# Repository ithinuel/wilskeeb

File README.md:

# Wil's Keyboard

This project implements a split keyboard based on the [Redox](https://github.com/mattdibi/redox-keyboard)
PCB but powered by a [SparkFun Pro Micro - RP2040](https://www.sparkfun.com/products/18288).

It features:

- Automatic main-secondary detection (either side can be connected to usb)
- Automatic chirality detection allowing the same binary to run on both sides.
- A virtual serial port to a simple CLI to help with debugging & update.
- 128x64 (SH1107 based) Oled display support

Extra optional features are also available:

- RGB Led strip

The communication between main & secondary is done through an I²C interface.

## Firmware deployment

On a fresh RP2040 enter into bootload by maintaining the boot button pressed while pressing reset.
Then run `cargo run --release` to compile and flash the firmware.

Refer to defmt documentation for available logging parameters.

I used the following command to update the firmware after the case is assembled and the buttons are
no-longer accessible.

```sh
DEFMT_BBQ_BUFFER_SIZE=4096 DEFMT_LOG=trace cargo build --release && echo -n u >> [your-uart] && sleep 5 && elf2uf2-rs -d target/thumbv6m-none-eabi/release/wilskeeb
```

## Layout

%2F%3B%3B&radii=20px&pcb:true&plate:false%3B&@_x:3.25&t=%23000000%0A%0A%23ff0000%3B&=%23%0A3%0AF3&_x:9&t=%23000000%3B&=*%0A8%3B&@_y:-0.875&x:2.25&t=%23000000%0A%0A%23ff0000%3B&=%2F@%0A2%0AF2&_x:1%3B&=$%0A4%0AF4&_x:7&t=%23000000%3B&=%2F&%0A7&_x:1%3B&=(%0A9%3B&@_y:-0.905&x:5.25&t=%23000000%0A%0A%23ff0000%3B&=%25%0A5%0AF5&_x:5&t=%23000000%3B&=%5E%0A6%3B&@_y:-0.845&a:5&w:1.25%3B&=~%0A%60&_t=%23000000%0A%0A%23ff0000&a:4%3B&=!%0A1%0AF1&_x:13&t=%23000000%3B&=)%0A0&_w:1.25%3B&=%7B%0A%5B%3B&@_y:-0.655&x:6.25&t=%23000000%0A%0A%23ff0000%3B&=%0A%0AF6&_x:3&t=%23000000&a:7%3B&=%3B&@_y:-0.72&x:3.25&t=%23000000%0A%0A%23ff0000&a:4%3B&=E%0A%0AF9&_x:9%3B&=I%0A%0A%3Ci%20class%2F='fa%20fa-arrow-up'%3E%3C%2F%2Fi%3E%3B&@_y:-0.875&x:2.25%3B&=W%0A%0AF8&_x:1%3B&=R%0A%0AF10&_x:7&fa@:0&:0&:5%3B%3B&=U%0A%0A%3Ci%20class%2F='kb%20kb-Arrows-Top-2'%3E%3C%2F%2Fi%3E&_x:1%3B&=O%0A%0A%3Ci%20class%2F='kb%20kb-Arrows-Bottom-2'%3E%3C%2F%2Fi%3E%3B&@_y:-0.905&x:5.25&f:3%3B&=T%0A%0AF11&_x:5&f:3%3B&=Y%0A%0A%3Ci%20class%2F='kb%20kb-Unicode-Page-Up-3'%3E%3C%2F%2Fi%3E%3B&@_y:-0.845&t=%23000000&a:7&fa@:7%3B&w:1.25%3B&=%3Ci%20class%2F='kb%20kb-Line-Start-End'%3E%3C%2F%2Fi%3E&_t=%23000000%0A%0A%23ff0000&a:4&f:3%3B&=Q%0A%0AF7%3B&@_y:-1&x:15.25&t=%23000000&f:3%3B&=P&_f:3&w:1.25%3B&=%7D%0A%5D%3B&@_y:-0.655&x:6.25&t=%23000000%0A%0A%23ff0000&h:1.5%3B&=%0A%0AF12&_x:3&t=%23000000&a:7&h:1.5%3B&=%3B&@_y:-0.72&x:3.25&a:4&f:3%3B&=D%3B&@_y:-1&x:13.25&t=%23000000%0A%0A%23ff0000&f:3%3B&=K%0A%0A%3Ci%20class%2F='fa%20fa-arrow-down'%3E%3C%2F%2Fi%3E%3B&@_y:-0.875&x:2.25&t=%23000000&f:3%3B&=S&_x:1&f:3&n:true%3B&=F&_x:7&t=%23000000%0A%0A%23ff0000%0A%23008000&f:3&n:true%3B&=J%0A%0A%3Ci%20class%2F='fa%20fa-arrow-left'%3E%3C%2F%2Fi%3E%0A%3Ci%20class%2F='kb%20kb-Multimedia-Rewind-Start'%3E%3C%2F%2Fi%3E&_x:1&f:3%3B&=L%0A%0A%3Ci%20class%2F='fa%20fa-arrow-right'%3E%3C%2F%2Fi%3E%0A%3Ci%20class%2F='kb%20kb-Multimedia-FastForward-End'%3E%3C%2F%2Fi%3E%3B&@_y:-0.9049999999999998&x:5.25&t=%23000000&f:3%3B&=G&_x:5&t=%23000000%0A%0A%23ff0000&fa@:0&:0&:5%3B%3B&=H%0A%0A%3Ci%20class%2F='kb%20kb-Unicode-Page-Down-3'%3E%3C%2F%2Fi%3E%3B&@_y:-0.8450000000000002&t=%23000000&a:7&w:1.25%3B&=Shift&_a:4%3B&=A&_x:13%3B&=%2F:%0A%2F%3B&_w:1.25%3B&=%2F@%0A'%3B&@_y:-0.375&x:3.25%3B&=C&_x:9%3B&=%3C%0A,%3B&@_y:-0.875&x:2.25%3B&=X&_x:1%3B&=V&_x:7%3B&=M&_x:1%3B&=%3E%0A.%3B&@_y:-0.9049999999999998&x:5.25%3B&=B&_x:5%3B&=N%3B&@_y:-0.8450000000000006&a:7&w:1.25%3B&=Ctrl&_a:4%3B&=Z&_x:13%3B&=%3F%0A%2F%2F&_w:1.25%3B&=~%0A%23%3B&@_y:-0.375&x:3.25&a:7%3B&=LAlt&_x:9&fa@:6%3B%3B&=%3Ci%20class%2F='fa%20fa-stack-overflow'%3E%3C%2F%2Fi%3E%3B&@_y:-0.875&x:2.25%3B&=&_x:11&a:4&f:3%3B&=%2F_%0A-%3B&@_y:-0.75&x:0.25&a:6&f:3%3B&=Pause&_f:3%3B&=PrtSc&_x:13&a:4&f:3%3B&=+%0A%2F=&_a:7&fa@:7%3B%3B&=%3Ci%20class%2F='fa%20fa-list-alt'%3E%3C%2F%2Fi%3E%3B&@_r:25&rx:5.135&ry:4.845&y:-0.5&x:-0.5&f:3%3B&=Esc%3B&@_r:30&rx:7.068&ry:4.875&y:-1&x:-1%3B&=&_f:3%3B&=Ins%3B&@_x:-1&f:3&h:1.5%3B&=%3Ci%20class%2F='kb%20kb-Return-2'%3E%3C%2F%2Fi%3E&_f:3&h:1.5%3B&=Space%3B&@_r:-30&rx:10.432&y:-1&x:-1&f:3%3B&=Del&_c=%232aa50a&f:3%3B&=Fn2%3B&@_x:-1&c=%23cccccc&f:3&h:1.5%3B&=%3Ci%20class%2F='kb%20kb-Arrows-Left'%3E%3C%2F%2Fi%3E&_c=%23ff0000&f:3&h:1.5%3B&=Fn1%3B&@_r:-25&rx:12.365&ry:4.845&y:-0.5&x:-0.5&c=%23cccccc&f:3%3B&=AltGr)

## Licenses

The hardware design files present in this repository under the `pcb` and `case` directories are
distributed under the [CERN OHL S v2 License](./cern_ohl_s_v2.txt).

```text
Copyright Wilfried Chauveau 2022.

This source describes Open Hardware and is licensed under the CERN-OHL-S v2.
You may redistribute and modify this source and make products using it under
the terms of the CERN-OHL-S v2 (https://ohwr.org/cern_ohl_s_v2.txt).

This source is distributed WITHOUT ANY EXPRESS OR IMPLIED WARRANTY, INCLUDING
OF MERCHANTABILITY, SATISFACTORY QUALITY AND FITNESS FOR A PARTICULAR PURPOSE.
Please see the CERN-OHL-S v2 for applicable conditions.

Source location: https://github.com/ithinuel/wilskeeb.git

As per CERN-OHL-S v2 section 4, should You produce hardware based on this source,
You must where practicable maintain the Source Location visible on the external
case of the Gizmo or other products you make using this source.
```

The sources available under the `firmware` directory are distributed under the
[Apache 2](./Apache-2.0.txt) license.

```text
Copyright 2022 Wilfried Chauveau

Licensed under the Apache License, Version 2.0 (the "License");
you may not use this file except in compliance with the License.
You may obtain a copy of the License at

    http://www.apache.org/licenses/LICENSE-2.0

Unless required by applicable law or agreed to in writing, software
distributed under the License is distributed on an "AS IS" BASIS,
WITHOUT WARRANTIES OR CONDITIONS OF ANY KIND, either express or implied.
See the License for the specific language governing permissions and
limitations under the License.
```

## Extra resources

- The 3D model for the Audio jack is available at : [Kicad-packages3D − MR#495](https://gitlab.com/kicad/libraries/kicad-packages3D/-/merge_requests/495)
- The PCB design for the OLED display can be found at : [Github − Adafruit OLED FeatherWing PCB](https://github.com/adafruit/Adafruit-OLED-FeatherWing-PCB.git)
- The PCB design for the Pro Micro RP2040 can be found at : [Github − SparkFun Pro Micro RP2040](https://github.com/sparkfun/SparkFun_Pro_Micro-RP2040.git)

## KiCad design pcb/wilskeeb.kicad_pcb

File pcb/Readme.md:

# PCD Design

## Option considered

- on board per key rgb LED using WS2812-2020  
  Those RGB LED draw up to 20mA and there would be 35 of them. This plus the rest of the system would
  exceed the capacity of the USB port.

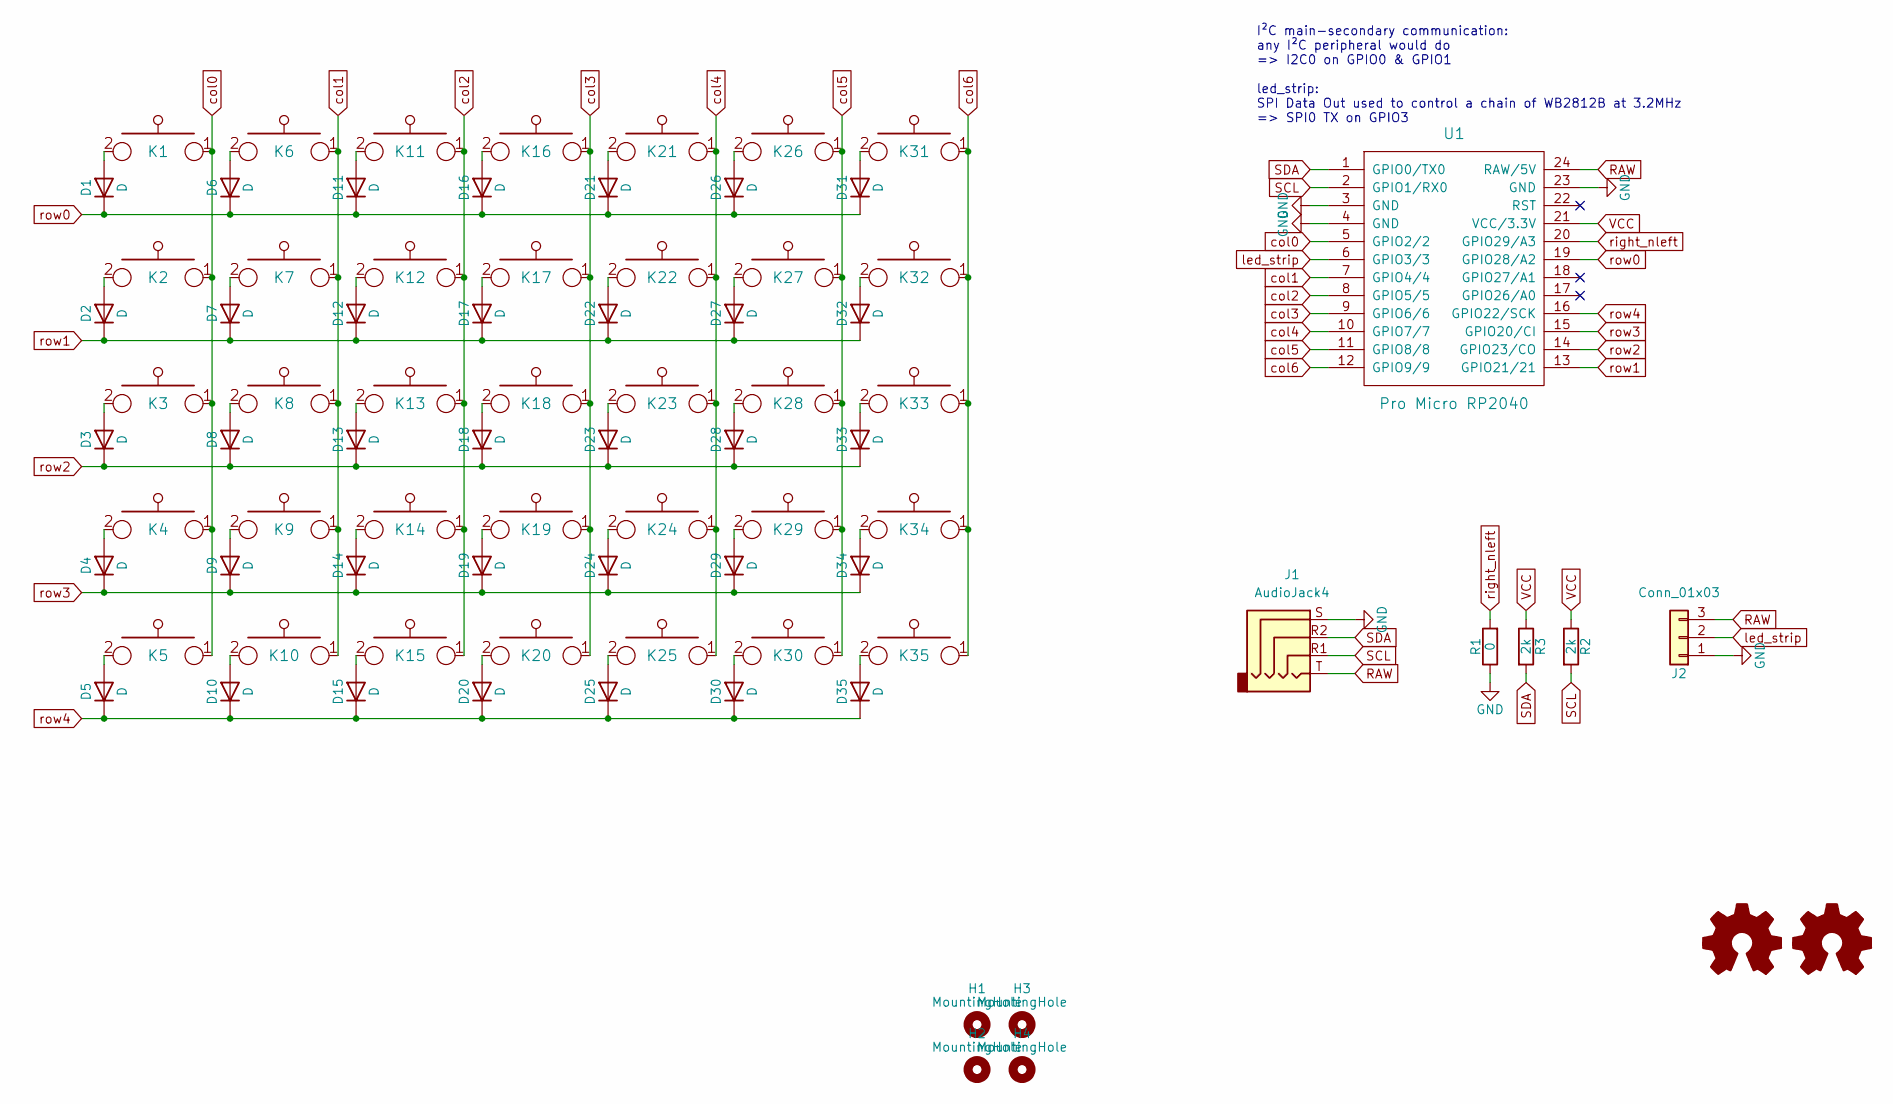
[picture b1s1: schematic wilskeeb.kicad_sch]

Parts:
D1, D2, D3, D4, D5, D6, D7, D8, D9, D10, D11, D12, D13, D14, D15, D16, D17, D18, D19, D20, D21, D22, D23, D24, D25, D26, D27, D28, D29, D30, D31, D32, D33, D34, D35: D; Diode-Hybrid-Reversible
H1, H2, H3, H4: MountingHole; MountingHole_3.2mm_M3_ISO14580
J1: AudioJack4; Jack_3.5mm_TRRS_PJ320D_Reversible
J2: Conn_01x03; PinHeader_1x03_P2.54mm_Horizontal
K1, K2, K3, K4, K5, K6, K7, K8, K9, K10, K11, K12, K13, K14, K15, K16, K17, K18, K19, K20, K21, K22, K23, K24, K25, K26, K27, K28, K29, K30, K31, K32, K33, K34, K35: KEYSW; PG1350-1u-Reversible
R1: 0; Resistor-Hybrid-Reversible
R2, R3: 2k; Resistor-Hybrid-Reversible
U1: Pro Micro RP2040; ProMicro-Reversible

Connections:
GND: J1.S, J2.1, R1.1, U1.3 (GND), U1.4 (GND), U1.23 (GND)
unnamed: D1.2 (A), K1.2
unnamed: D2.2 (A), K2.2
unnamed: D3.2 (A), K3.2
unnamed: D4.2 (A), K4.2
unnamed: D5.2 (A), K5.2
unnamed: D6.2 (A), K6.2
unnamed: D7.2 (A), K7.2
unnamed: D8.2 (A), K8.2
unnamed: D9.2 (A), K9.2
unnamed: D10.2 (A), K10.2
unnamed: D11.2 (A), K11.2
unnamed: D12.2 (A), K12.2
unnamed: D13.2 (A), K13.2
unnamed: D14.2 (A), K14.2
unnamed: D15.2 (A), K15.2
unnamed: D16.2 (A), K16.2
unnamed: D17.2 (A), K17.2
unnamed: D18.2 (A), K18.2
unnamed: D19.2 (A), K19.2
unnamed: D20.2 (A), K20.2
unnamed: D21.2 (A), K21.2
unnamed: D22.2 (A), K22.2
unnamed: D23.2 (A), K23.2
unnamed: D24.2 (A), K24.2
unnamed: D25.2 (A), K25.2
unnamed: D26.2 (A), K26.2
unnamed: D27.2 (A), K27.2
unnamed: D28.2 (A), K28.2
unnamed: D29.2 (A), K29.2
unnamed: D30.2 (A), K30.2
unnamed: D31.2 (A), K31.2
unnamed: D32.2 (A), K32.2
unnamed: D33.2 (A), K33.2
unnamed: D34.2 (A), K34.2
unnamed: D35.2 (A), K35.2
RAW: J1.T, J2.3, U1.24 (RAW/5V)
SCL: J1.R1, R2.2, U1.2 (GPIO1/RX0)
SDA: J1.R2, R3.2, U1.1 (GPIO0/TX0)
VCC: R2.1, R3.1, U1.21 (VCC/3.3V)
col0: K1.1, K2.1, K3.1, K4.1, K5.1, U1.5 (GPIO2/2)
col1: K6.1, K7.1, K8.1, K9.1, K10.1, U1.7 (GPIO4/4)
col2: K11.1, K12.1, K13.1, K14.1, K15.1, U1.8 (GPIO5/5)
col3: K16.1, K17.1, K18.1, K19.1, K20.1, U1.9 (GPIO6/6)
col4: K21.1, K22.1, K23.1, K24.1, K25.1, U1.10 (GPIO7/7)
col5: K26.1, K27.1, K28.1, K29.1, K30.1, U1.11 (GPIO8/8)
col6: K31.1, K32.1, K33.1, K34.1, K35.1, U1.12 (GPIO9/9)
led_strip: J2.2, U1.6 (GPIO3/3)
right_nleft: R1.2, U1.20 (GPIO29/A3)
row0: D1.1 (K), D6.1 (K), D11.1 (K), D16.1 (K), D21.1 (K), D26.1 (K), D31.1 (K), U1.19 (GPIO28/A2)
row1: D2.1 (K), D7.1 (K), D12.1 (K), D17.1 (K), D22.1 (K), D27.1 (K), D32.1 (K), U1.13 (GPIO21/21)
row2: D3.1 (K), D8.1 (K), D13.1 (K), D18.1 (K), D23.1 (K), D28.1 (K), D33.1 (K), U1.14 (GPIO23/CO)
row3: D4.1 (K), D9.1 (K), D14.1 (K), D19.1 (K), D24.1 (K), D29.1 (K), D34.1 (K), U1.15 (GPIO20/CI)
row4: D5.1 (K), D10.1 (K), D15.1 (K), D20.1 (K), D25.1 (K), D30.1 (K), D35.1 (K), U1.16 (GPIO22/SCK)

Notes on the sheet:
I²C main-secondary communication: any I²C peripheral would do => I2C0 on GPIO0 & GPIO1 led_strip: SPI Data Out used to control a chain of WB2812B at 3.2MHz => SPI0 TX on GPIO3

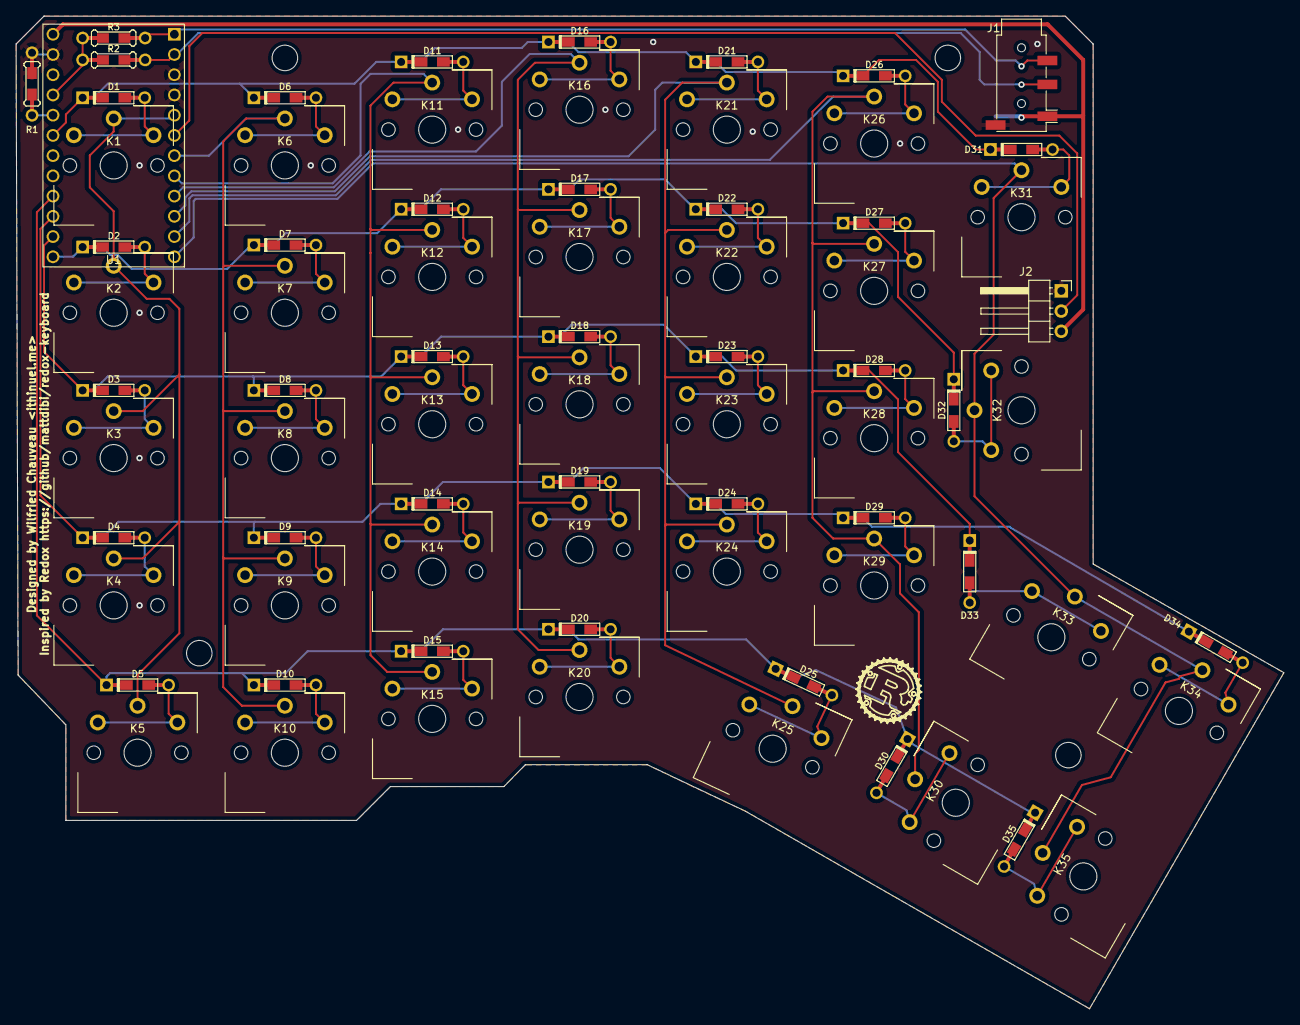
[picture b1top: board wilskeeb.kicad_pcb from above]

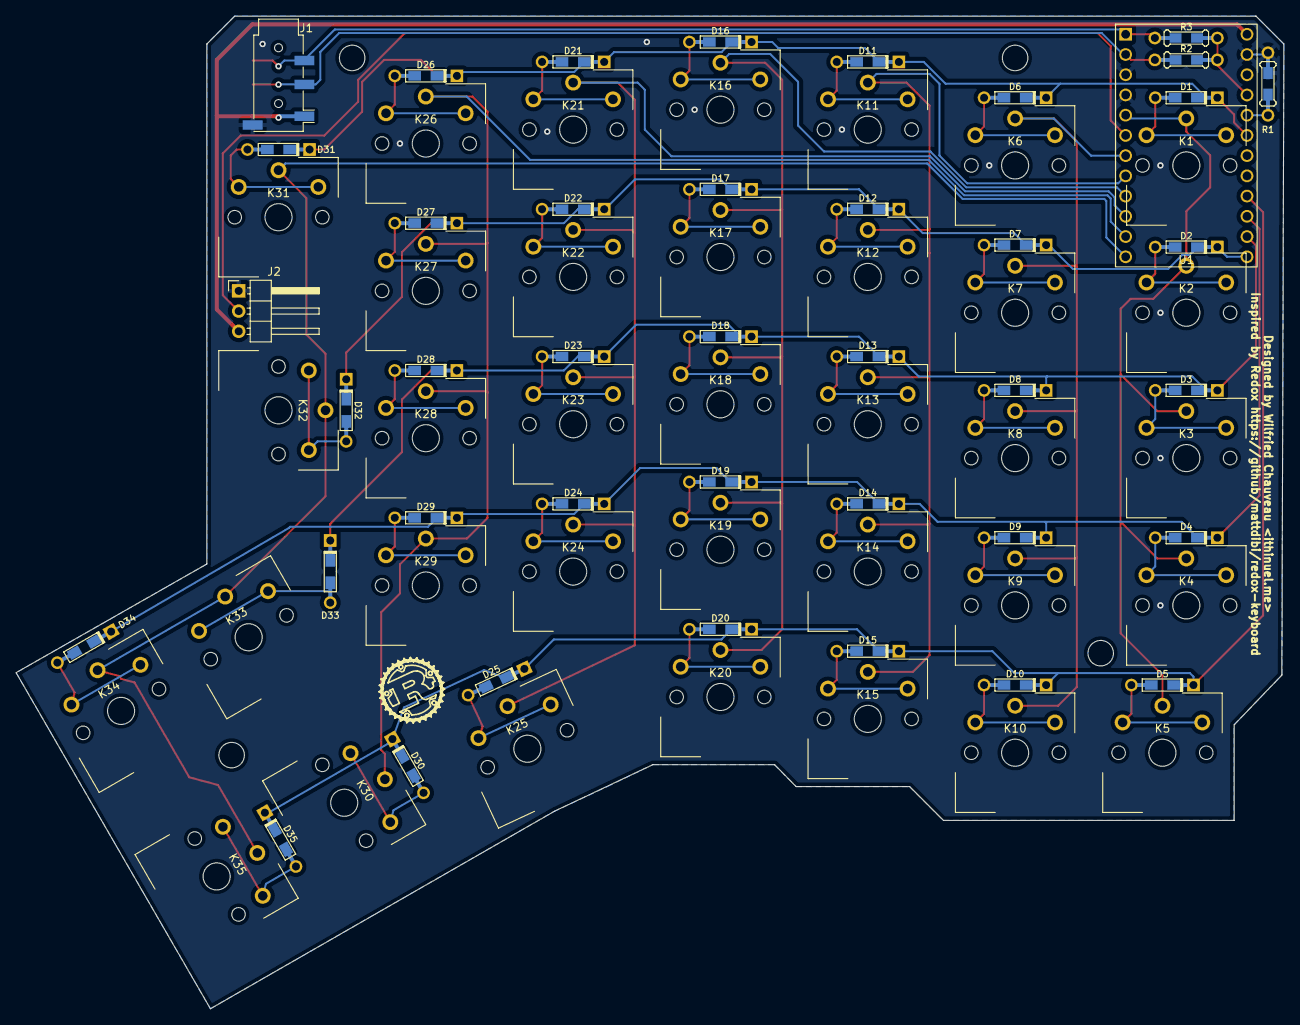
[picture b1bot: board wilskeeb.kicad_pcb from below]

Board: 2 copper layers, 159.1 x 124.6 mm, 80 parts (2 on the bottom side), 54 nets.

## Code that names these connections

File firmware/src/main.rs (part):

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    (scanned, to_usb): (&RefCell<ScannedEventStack>, &RefCell<ToUSBStack>),
    system_clock: &rp2040_hal::clocks::SystemClock,
    i2c_block: pac::I2C0,
    sda: Pin<bank0::Gpio0, FunctionNull, PullDown>,
    scl: Pin<bank0::Gpio1, FunctionNull, PullDown>,
    resets: pac::RESETS,
    timer: &Timer,
) {
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    #[cfg(feature = "debug-to-cli")]
    let consumer = defmt_bbq::init().unwrap_or_else(|_| unreachable!());

    // GPIO0-1: SDA/SCL: inter-chip com (i2c0)
    // GPIO2: col0
    // GPIO3: RGB data                  (pio0-sm1)
    // GPIO4-9: col 1-6
    // GPIO16-17: SDA/SCL: oled display (pio1)
    // GPIO28, 21, 23, 20, 22: row0-4
    // GPIO25: WS2812 onboard addressable rgb (pio0-sm0)
    // GPIO29: right_nleft: high = right half

    use embedded_hal::digital::InputPin;
    let mut pin = pins.gpio29.into_pull_up_input(); // setup pull-up input
                                                    // give a little bit of time for the pull-up to do its job.
    cortex_m::asm::delay(500);
    let is_right = pin.is_high().unwrap_or_else(|_| unreachable!()); // Cannot fail
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    ));

    #[allow(unused_mut)]
    let (mut resets, i2c, sda, scl) = (pac.RESETS, pac.I2C0, pins.gpio0, pins.gpio1);

    #[cfg(feature = "ui")]
    let (
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        (
            pac.PIO0.split(&mut resets),
            pac.PIO1.split(&mut resets),
            (pins.gpio25, pins.gpio3),
            (pins.gpio16, pins.gpio17),
        )
    };

    let mut matrix = matrix::Matrix::new(
        (
            pins.gpio2.into_pull_up_input(),
            pins.gpio4.into_pull_up_input(),
            pins.gpio5.into_pull_up_input(),
            pins.gpio6.into_pull_up_input(),
            pins.gpio7.into_pull_up_input(),
            pins.gpio8.into_pull_up_input(),
            pins.gpio9.into_pull_up_input(),
        ),
        (
            pins.gpio28.reconfigure(),
            pins.gpio21.reconfigure(),
            pins.gpio23.reconfigure(),
            pins.gpio20.reconfigure(),
            pins.gpio22.reconfigure(),
        ),
    );

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
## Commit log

2022-04-17 Initiate work on UI, remove dependency on embassy, use rp2040-async-i2c
2022-04-17 Update layout.
2022-04-17 add DEFMT config to .cargo/config
2022-04-17 lock embedded-hal's revision
2022-04-17 bump dependencies revisions
2022-04-17 fix debug build
2022-04-18 --wip-- [skip ci]
2022-05-03 bump keyberon, allow entering bootloader from layer3
2022-05-03 make the usb-serial optionnal
2022-08-29 update submodules & change the menu key to ScrollLock
2022-08-29 bump hal versions
2022-08-29 use a fork of bbqueue that uses a more recent version of cortex-m
2022-08-29 adjust layout. % was in an awkward position.
2022-08-29 migrate keyberon's HidClass to usbd-human-interface-device
2022-08-29 clean up logs
2022-08-29 add support for suspend and remote wake up
2022-08-29 overhaul features
    Use debug-to-cli or debug-to-probe to enable defmt traces
    Use cli to enable usb-serial peripheral
    debug-to-cli enables cli
2022-08-29 Apply clippy's suggestions
2022-08-29 update dependencies and enable rp2040 errata5 support
2022-08-29 remove unnecessary dependency.
    u8s are already well optimised by the compiler, there is no need for
    num-interger
2022-08-29 Add missing read_report.
    If this is not called, the report sent by the host (report led state)
    remains in the usb block's mailbox preventing it from entering suspend.
2022-08-29 migrate to fugit
2022-08-29 use upstream rp2040-hal <3
2022-08-29 Make the app actually async and rely on on interrupt for blocking operations.
2023-11-09 update deps
2023-11-29 remove sh1107_wrapper in favor of i2c-write-iter
2026-03-22 Add flake.nix to allow reproducible build
